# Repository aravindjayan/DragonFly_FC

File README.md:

# DragonFly Flight Controller

DragonFly Flight Controller is an open hardware, low-cost flight controller PCB and experimentation platform for UAV, drone, and embedded systems prototyping. This cost-optimised design uses a two-layer PCB, a budget-conscious bill of materials (BOM), and readily fabricated manufacturing files. Prototype boards were fabricated using the LionCircuits MII service.

The KiCad design targets broad sensor compatibility: it supports most ST LSM6D-series IMUs, while the magnetometer footprint accommodates QMC5883, HMC5883, MMC5983, and IST8310 parts. This makes DragonFly a flexible platform for flight-control experiments, sensor evaluation, and affordable PCB prototyping.

## Repository contents

- `KiCad/Source/` — editable V0.1 board, hierarchical schematic sheets, and project settings.
- `KiCad/Production/` — PCB and project settings for the released `withRibs` manufacturing revision used to generate the production Gerbers.
- `Manufacturing/Gerbers/` — production Gerber layers, drill files, drill maps, and KiCad job file.
- `Photos/` — photo of the assembled PCB.

## Fabrication

Send all files in `Manufacturing/Gerbers/` to your PCB fabricator as one fabrication package. The set includes front and back copper, solder mask, silkscreen, paste, board outline, plated and non-plated drill files, drill maps, and the Gerber job file. Confirm your fabricator accepts these Gerber formats and review the generated previews before ordering.

The released board includes an external rib frame (`withRibs`) for fabrication. Use the matching board in `KiCad/Production/` when reviewing this manufacturing package. `KiCad/Source/` retains the editable source project from the main V0.1 design directory.

## Opening the design

Open `KiCad/Source/dragonfly_v0_1.kicad_pro` in KiCad to work with the source design. Open `KiCad/Production/Dragonfly_v0-1_Ribs.kicad_pcb` to inspect the exact released manufacturing board.

## Revision notes

The production files are from the V0.1 `withRibs` release. The original release notes describe it as adding an external rib frame for improved fabrication. Review electrical design, clearances, and fabrication outputs independently before manufacturing or flight use.

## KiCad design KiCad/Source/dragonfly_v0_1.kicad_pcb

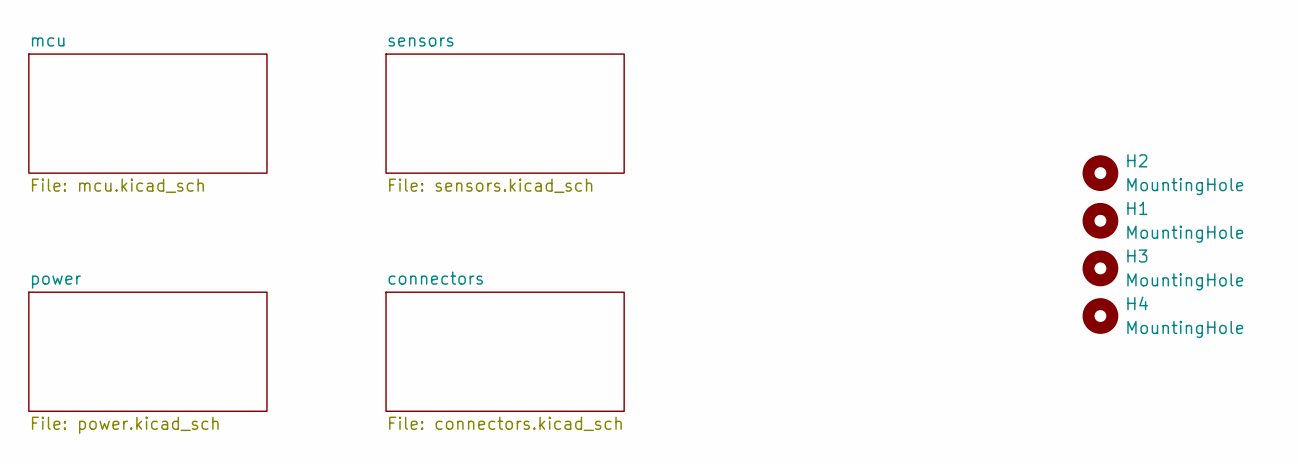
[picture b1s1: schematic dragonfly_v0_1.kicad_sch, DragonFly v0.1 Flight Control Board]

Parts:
H1, H2, H3, H4: MountingHole; MountingHole_2.2mm_M2_ISO14580

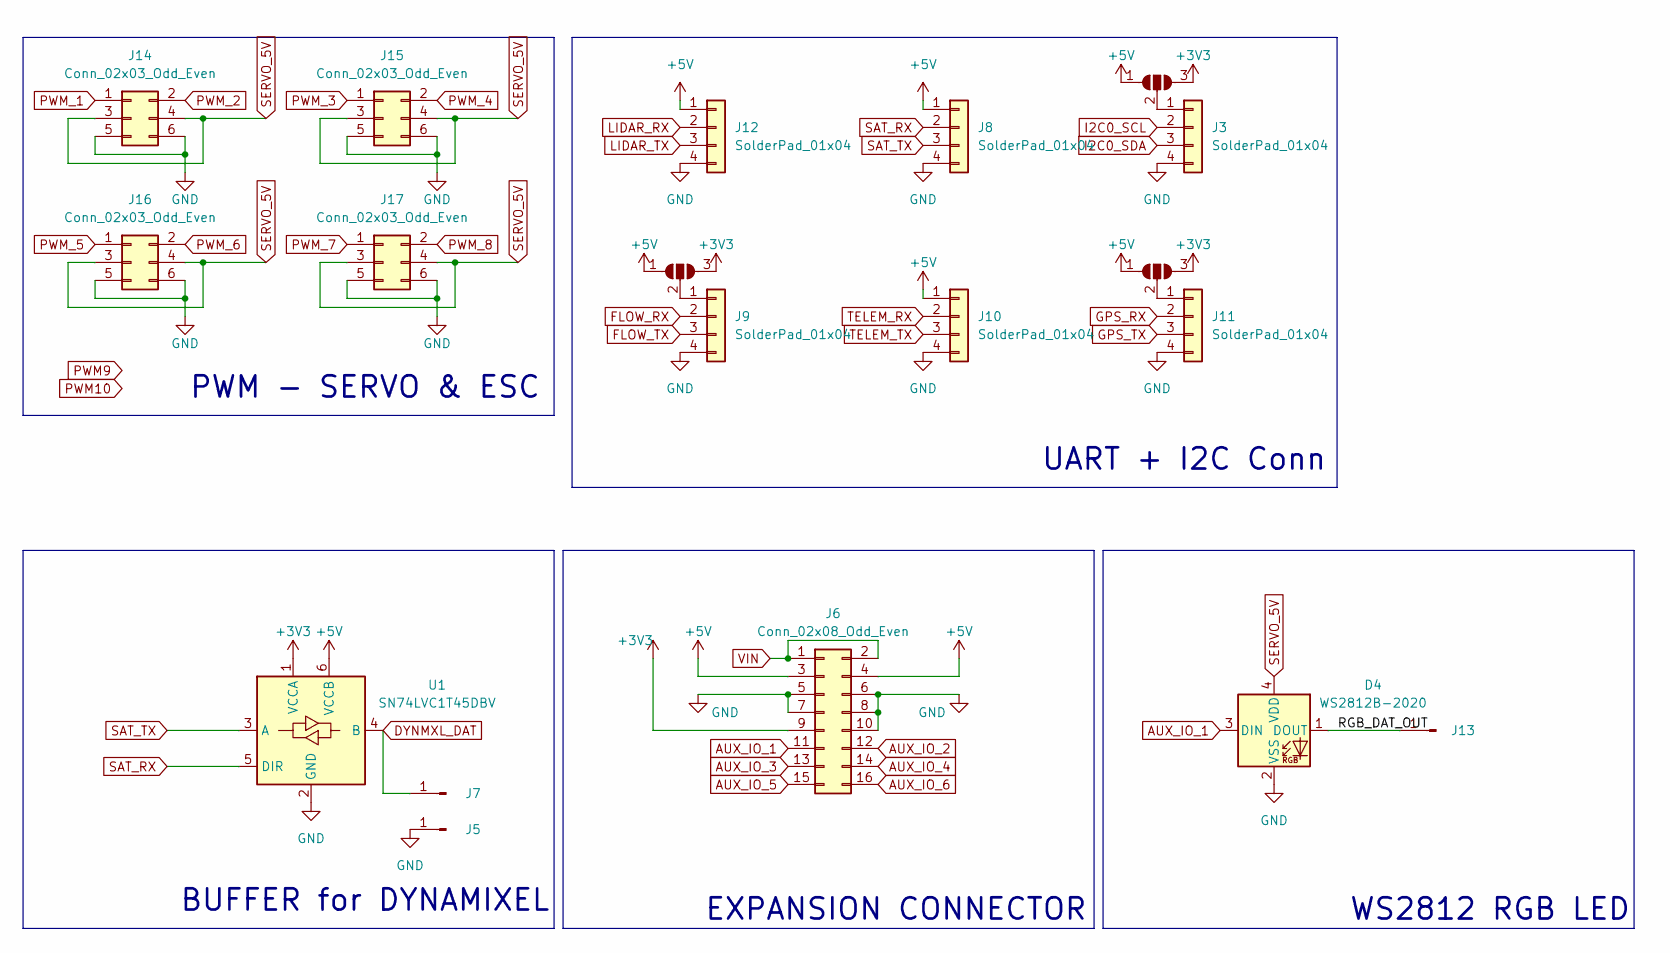
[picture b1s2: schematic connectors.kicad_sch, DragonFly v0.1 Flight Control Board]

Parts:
D4: WS2812B-2020; LED_WS2812B-2020_PLCC4_2.0x2.0mm
J3, J8, J9, J10, J11, J12: SolderPad_01x04; 4pad_doubleSide_rect_1.7x2mm
J5, J7, J13: SolderPad; SolderWirePad_1x01_SMD_1x2mm
J6: Conn_02x08_Odd_Even; PinSocket_2x08_P2.54mm_Vertical
J14, J15, J16, J17: Conn_02x03_Odd_Even; dragonfly_conn_2x3_graphics
JP1, JP2, JP3: SolderJumper_3_Open; SolderJumper-3_P1.3mm_Open_RoundedPad1.0x1.5mm
U1: SN74LVC1T45DBV; SOT-23-6

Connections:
+3V3: J6.9, JP1.3 (B), JP2.3 (B), JP3.3 (B), U1.1 (VCCA); also elsewhere on the board
+5V: J6.3, J6.4, J8.1, J10.1, J12.1, JP1.1 (A), JP2.1 (A), JP3.1 (A), U1.6 (VCCB); also elsewhere on the board
/connectors/RGB_DAT_OUT: D4.1 (DOUT), J13.1
AUX_IO_1: D4.3 (DIN), J6.11; also elsewhere on the board
AUX_IO_2: J6.12; also elsewhere on the board
AUX_IO_3: J6.13; also elsewhere on the board
AUX_IO_4: J6.14; also elsewhere on the board
AUX_IO_5: J6.15; also elsewhere on the board
AUX_IO_6: J6.16; also elsewhere on the board
DYNMXL_DAT: J7.1, U1.4 (B)
FLOW_RX: J9.2; also elsewhere on the board
FLOW_TX: J9.3; also elsewhere on the board
GND: D4.2 (VSS), J3.4, J5.1, J6.5, J6.6, J6.7, J6.8, J6.10, J8.4, J9.4, J10.4, J11.4, J12.4, J14.5, J14.6, J15.5, J15.6, J16.5, J16.6, J17.5, J17.6, U1.2 (GND); also elsewhere on the board
GPS_RX: J11.2; also elsewhere on the board
GPS_TX: J11.3; also elsewhere on the board
I2C0_SCL: J3.2; also elsewhere on the board
I2C0_SDA: J3.3; also elsewhere on the board
LIDAR_RX: J12.2; also elsewhere on the board
LIDAR_TX: J12.3; also elsewhere on the board
unnamed: J3.1, JP1.2 (C)
unnamed: J9.1, JP2.2 (C)
unnamed: J11.1, JP3.2 (C)
PWM_1: J14.1; also elsewhere on the board
PWM_2: J14.2; also elsewhere on the board
PWM_3: J15.1; also elsewhere on the board
PWM_4: J15.2; also elsewhere on the board
PWM_5: J16.1; also elsewhere on the board
PWM_6: J16.2; also elsewhere on the board
PWM_7: J17.1; also elsewhere on the board
PWM_8: J17.2; also elsewhere on the board
SAT_RX: J8.2, U1.5 (DIR); also elsewhere on the board
SAT_TX: J8.3, U1.3 (A); also elsewhere on the board
SERVO_5V: D4.4 (VDD), J14.3, J14.4, J15.3, J15.4, J16.3, J16.4, J17.3, J17.4; also elsewhere on the board
TELEM_RX: J10.2; also elsewhere on the board
TELEM_TX: J10.3; also elsewhere on the board
VIN: J6.1, J6.2; also elsewhere on the board

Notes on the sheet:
UART + I2C Conn
EXPANSION CONNECTOR
PWM - SERVO & ESC
WS2812 RGB LED
BUFFER for DYNAMIXEL

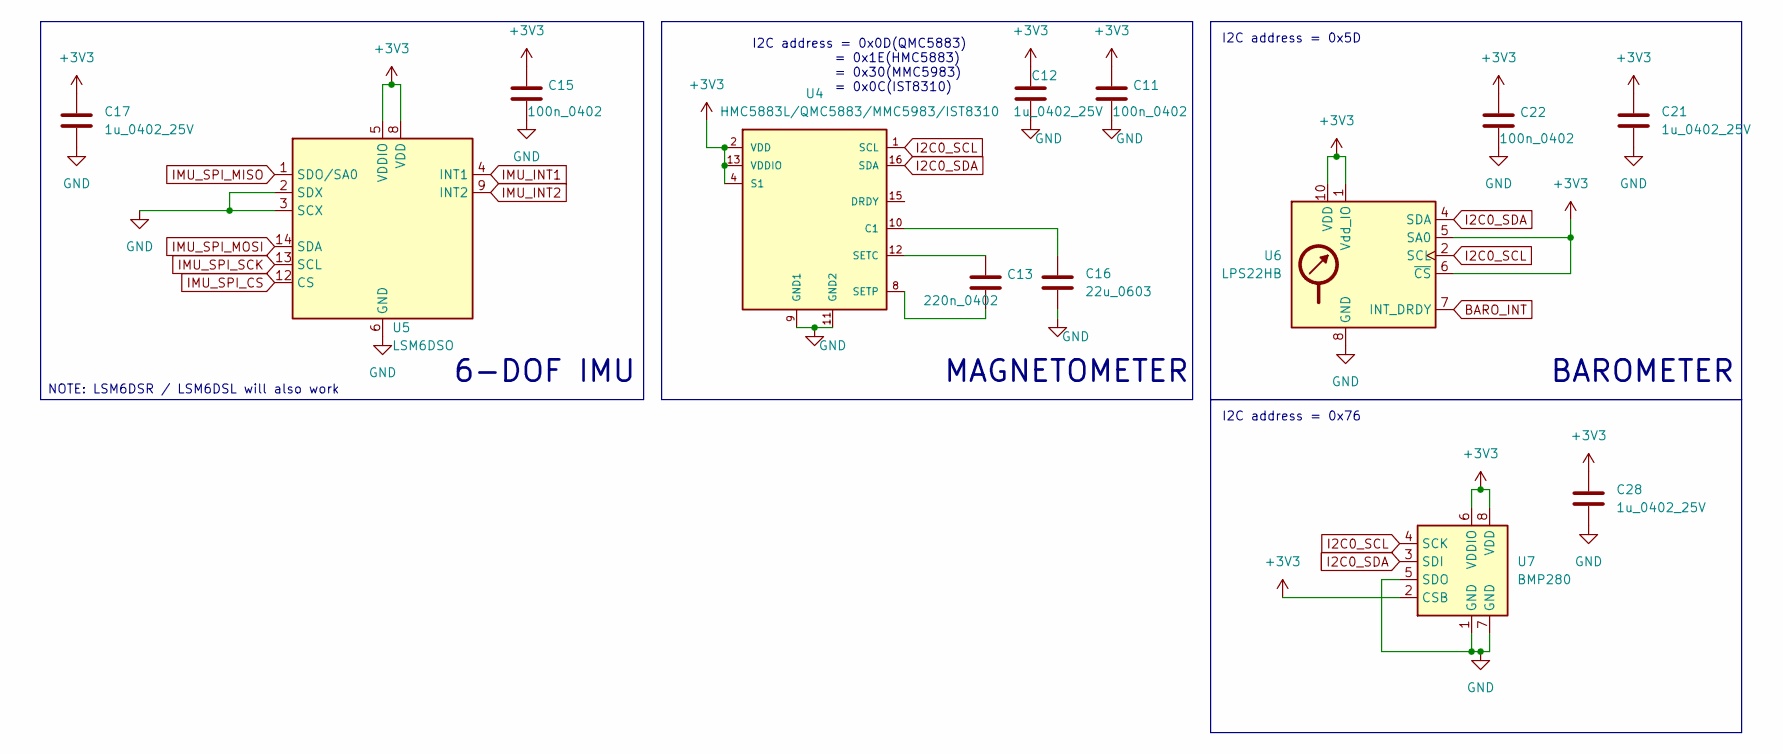
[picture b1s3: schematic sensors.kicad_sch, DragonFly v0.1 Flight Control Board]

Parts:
C11, C15, C22: 100n_0402; C_0402_1005Metric
C12, C17, C21, C28: 1u_0402_25V; C_0402_1005Metric
C13: 220n_0402; C_0402_1005Metric
C16: 22u_0603; C_0603_1608Metric
U4: HMC5883L/QMC5883/MMC5983/IST8310; HMC5883L
U5: LSM6DSO; LGA-14_3x2.5mm_P0.5mm_LayoutBorder3x4y
U6: LPS22HB; LPS22_HLGA10_SNAPEDA
U7: BMP280; BMP280_Bosch_LGA-8_2x2.5mm_P0.65mm_ClockwisePinNumbering

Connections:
+3V3: C11.1, C12.1, C15.1, C17.1, C21.1, C22.1, C28.1, U4.2 (VDD), U4.4 (S1), U4.13 (VDDIO), U5.5 (VDDIO), U5.8 (VDD), U6.1 (Vdd_IO), U6.5 (SA0), U6.6 (~CS), U6.10 (VDD), U7.2 (CSB), U7.6 (VDDIO), U7.8 (VDD); also elsewhere on the board
BARO_INT: U6.7 (INT_DRDY)
GND: C11.2, C12.2, C15.2, C16.2, C17.2, C21.2, C22.2, C28.2, U4.9 (GND1), U4.11 (GND2), U5.2 (SDX), U5.3 (SCX), U5.6 (GND), U5.7 (GND), U6.3 (GND), U6.8 (GND), U6.9 (GND), U7.1 (GND), U7.5 (SDO), U7.7 (GND); also elsewhere on the board
I2C0_SCL: U4.1 (SCL), U6.2 (SCL), U7.4 (SCK); also elsewhere on the board
I2C0_SDA: U4.16 (SDA), U6.4 (SDA), U7.3 (SDI); also elsewhere on the board
IMU_INT1: U5.4 (INT1)
IMU_INT2: U5.9 (INT2)
IMU_SPI_CS: U5.12 (CS); also elsewhere on the board
IMU_SPI_MISO: U5.1 (SDO/SA0); also elsewhere on the board
IMU_SPI_MOSI: U5.14 (SDA); also elsewhere on the board
IMU_SPI_SCK: U5.13 (SCL); also elsewhere on the board
unnamed: C16.1, U4.10 (C1)
unnamed: C13.1, U4.12 (SETC)
unnamed: C13.2, U4.8 (SETP)

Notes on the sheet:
BAROMETER
NOTE: LSM6DSR / LSM6DSL will also work
I2C address = 0x0D(QMC5883) = 0x1E(HMC5883) = 0x30(MMC5983) = 0x0C(IST8310)
I2C address = 0x76
6-DOF IMU
MAGNETOMETER
I2C address = 0x5D

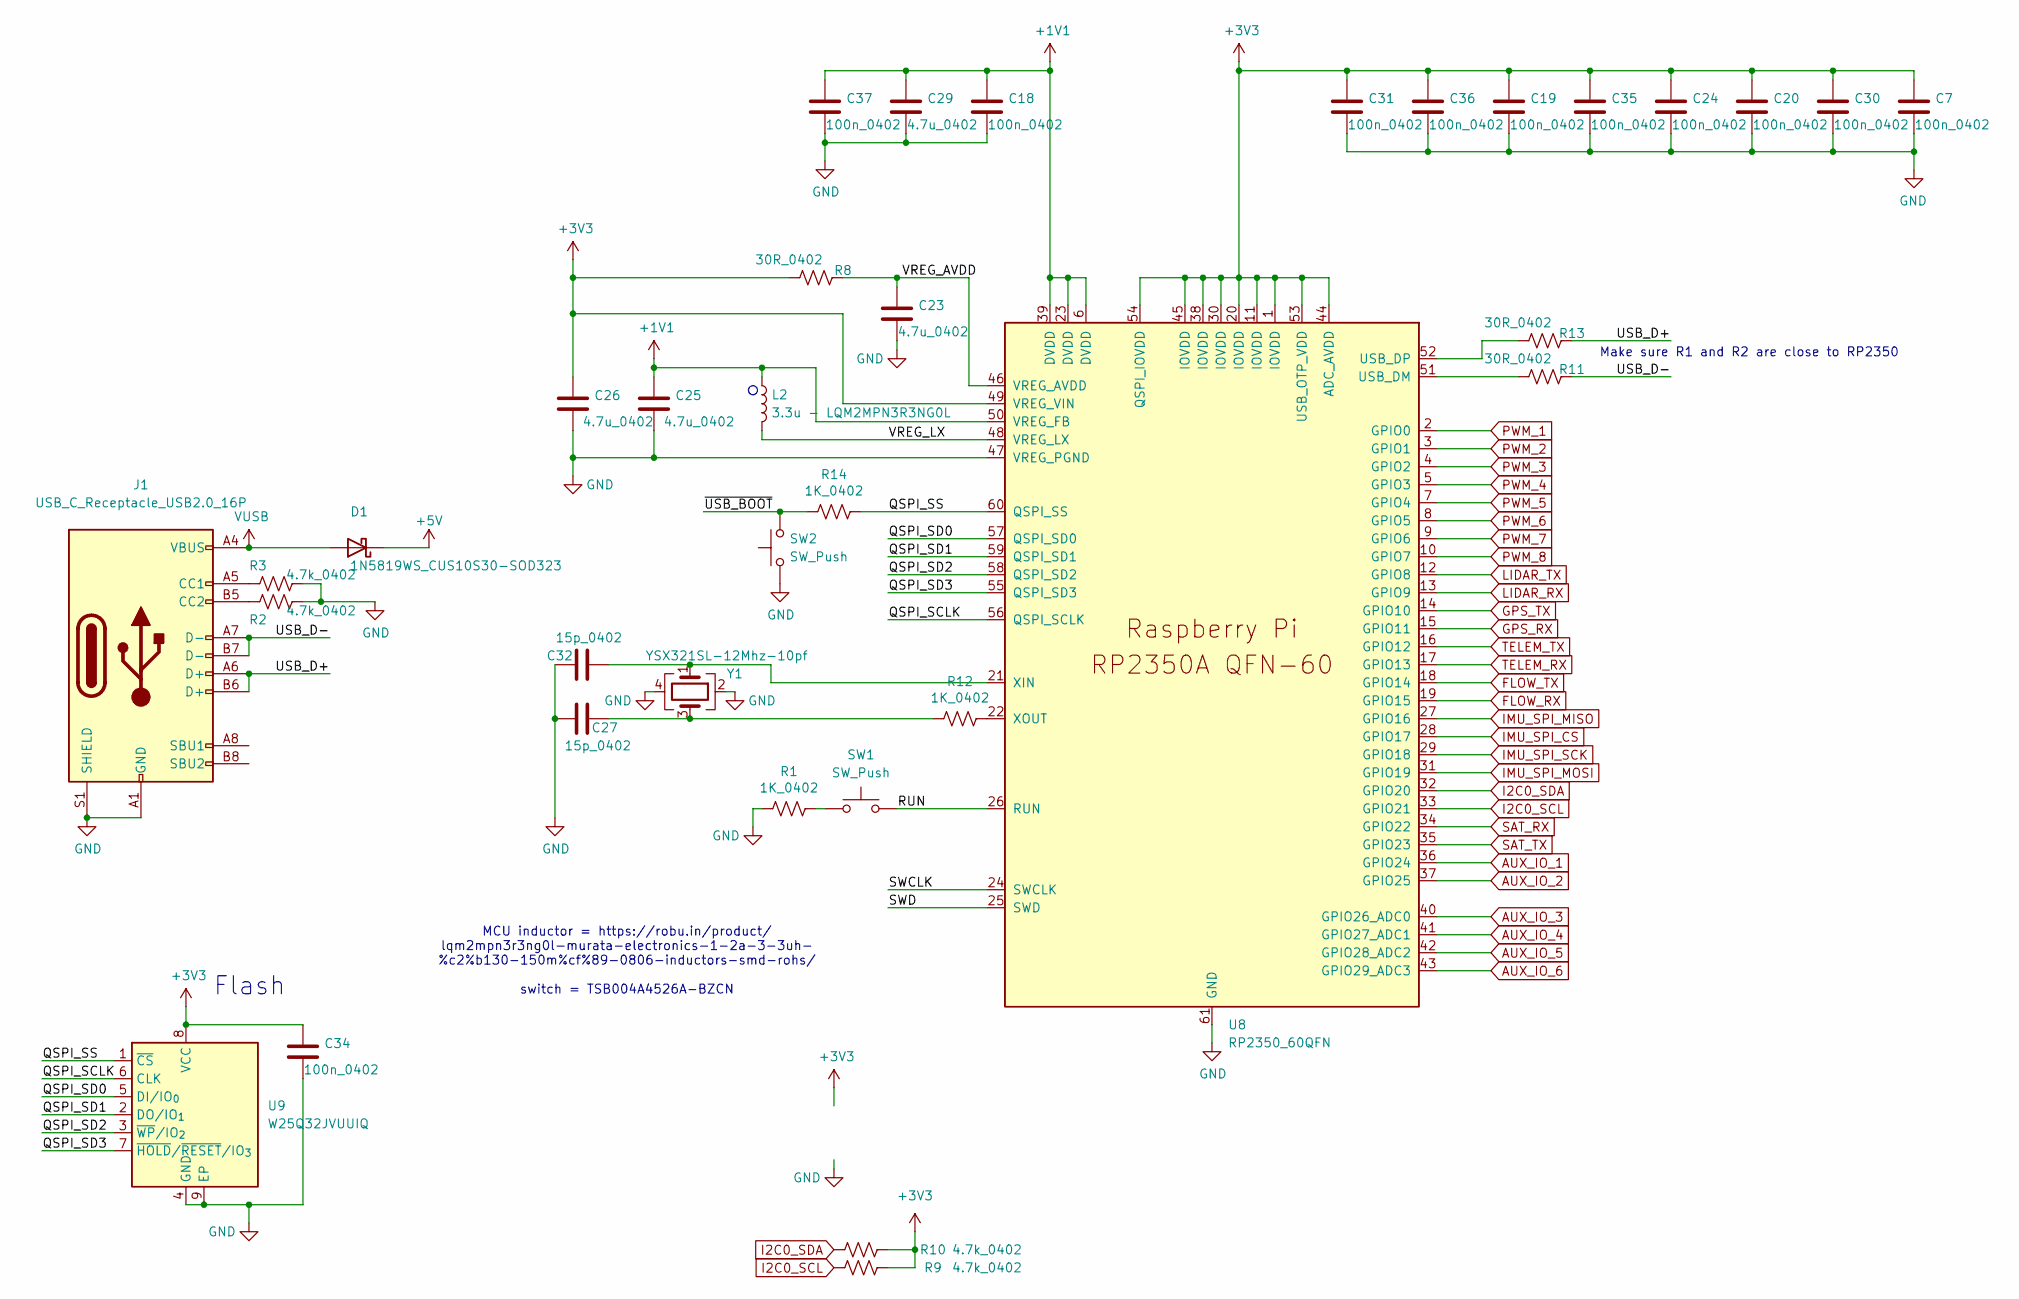
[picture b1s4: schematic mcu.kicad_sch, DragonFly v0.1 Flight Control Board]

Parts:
C7, C18, C19, C20, C24, C30, C31, C34, C35, C36, C37: 100n_0402; C_0402_1005Metric
C23, C29: 4.7u_0402; C_0402_1005Metric
C25, C26: 4.7u_0402; C_0402_SmallPads
C27, C32: 15p_0402; C_0402_1005Metric
D1: 1N5819WS_CUS10S30-SOD323; D_SOD-323
J1: USB_C_Receptacle_USB2.0_16P; USB_C_Receptacle_XKB_U262-16XN-4BVC11
L2: 3.3u - LQM2MPN3R3NG0L; L_Murata_DFE201610P
R1, R12, R14: 1K_0402; R_0402_1005Metric
R2, R3, R9, R10: 4.7k_0402; R_0402_1005Metric
R8, R11, R13: 30R_0402; R_0402_1005Metric
SW1, SW2: SW_Push; rightAngle_Switch_MJTP1117
U8: RP2350_60QFN; QFN-60-1EP_7x7mm_P0.4mm_EP3.4x3.4mm_ThermalVias_RP2350
U9: W25Q32JVUUIQ; Winbond_USON-8-2EP_3x4mm_P0.8mm_EP0.2x0.8mm
Y1: YSX321SL-12Mhz-10pf; Crystal_SMD_3225-4Pin_3.2x2.5mm

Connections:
+1V1: C18.1, C25.1, C29.1, C37.1, L2.1, U8.6 (DVDD), U8.23 (DVDD), U8.39 (DVDD), U8.50 (VREG_FB)
+3V3: C7.1, C19.1, C20.1, C24.1, C26.1, C30.1, C31.1, C34.1, C35.1, C36.1, R8.2, R9.1, R10.1, U8.1 (IOVDD), U8.11 (IOVDD), U8.20 (IOVDD), U8.30 (IOVDD), U8.38 (IOVDD), U8.44 (ADC_AVDD), U8.45 (IOVDD), U8.49 (VREG_VIN), U8.53 (USB_OTP_VDD), U8.54 (QSPI_IOVDD), U9.8 (VCC); also elsewhere on the board
+5V: D1.1 (K); also elsewhere on the board
/mcu/QSPI_SCLK: U8.56 (QSPI_SCLK), U9.6 (CLK)
/mcu/QSPI_SD0: U8.57 (QSPI_SD0), U9.5 (DI/IO_{0})
/mcu/QSPI_SD1: U8.59 (QSPI_SD1), U9.2 (DO/IO_{1})
/mcu/QSPI_SD2: U8.58 (QSPI_SD2), U9.3 (~WP/IO_{2})
/mcu/QSPI_SD3: U8.55 (QSPI_SD3), U9.7 (~HOLD/~RESET/IO_{3})
/mcu/QSPI_SS: R14.1, U8.60 (QSPI_SS), U9.1 (~CS)
/mcu/RUN: SW1.2, U8.26 (RUN)
/mcu/SWCLK: U8.24 (SWCLK)
/mcu/SWD: U8.25 (SWD)
/mcu/USB_D+: J1.A6 (D+), J1.B6 (D+), R13.1
/mcu/USB_D-: J1.A7 (D-), J1.B7 (D-), R11.1
/mcu/VREG_AVDD: C23.1, R8.1, U8.46 (VREG_AVDD)
/mcu/VREG_LX: L2.2, U8.48 (VREG_LX)
/mcu/~USB_BOOT: R14.2, SW2.2
AUX_IO_1: U8.36 (GPIO24); also elsewhere on the board
AUX_IO_2: U8.37 (GPIO25); also elsewhere on the board
AUX_IO_3: U8.40 (GPIO26_ADC0); also elsewhere on the board
AUX_IO_4: U8.41 (GPIO27_ADC1); also elsewhere on the board
AUX_IO_5: U8.42 (GPIO28_ADC2); also elsewhere on the board
AUX_IO_6: U8.43 (GPIO29_ADC3); also elsewhere on the board
FLOW_RX: U8.19 (GPIO15); also elsewhere on the board
FLOW_TX: U8.18 (GPIO14); also elsewhere on the board
GND: C7.2, C18.2, C19.2, C20.2, C23.2, C24.2, C25.2, C26.2, C27.2, C29.2, C30.2, C31.2, C32.2, C34.2, C35.2, C36.2, C37.2, J1.A1 (GND), J1.A12 (GND), J1.B1 (GND), J1.B12 (GND), J1.S1 (SHIELD), R1.2, R2.1, R3.1, SW2.1, U8.47 (VREG_PGND), U8.61 (GND), U9.4 (GND), U9.9 (EP), Y1.2, Y1.4; also elsewhere on the board
GPS_RX: U8.15 (GPIO11); also elsewhere on the board
GPS_TX: U8.14 (GPIO10); also elsewhere on the board
I2C0_SCL: R9.2, U8.33 (GPIO21); also elsewhere on the board
I2C0_SDA: R10.2, U8.32 (GPIO20); also elsewhere on the board
IMU_SPI_CS: U8.28 (GPIO17); also elsewhere on the board
IMU_SPI_MISO: U8.27 (GPIO16); also elsewhere on the board
IMU_SPI_MOSI: U8.31 (GPIO19); also elsewhere on the board
IMU_SPI_SCK: U8.29 (GPIO18); also elsewhere on the board
LIDAR_RX: U8.13 (GPIO9); also elsewhere on the board
LIDAR_TX: U8.12 (GPIO8); also elsewhere on the board
unnamed: C27.1, R12.2, Y1.3
unnamed: J1.A5 (CC1), R3.2
unnamed: J1.B5 (CC2), R2.2
unnamed: R1.1, SW1.1
unnamed: R11.2, U8.51 (USB_DM)
unnamed: R13.2, U8.52 (USB_DP)
unnamed: C32.1, U8.21 (XIN), Y1.1
unnamed: R12.1, U8.22 (XOUT)
PWM_1: U8.2 (GPIO0); also elsewhere on the board
PWM_2: U8.3 (GPIO1); also elsewhere on the board
PWM_3: U8.4 (GPIO2); also elsewhere on the board
PWM_4: U8.5 (GPIO3); also elsewhere on the board
PWM_5: U8.7 (GPIO4); also elsewhere on the board
PWM_6: U8.8 (GPIO5); also elsewhere on the board
PWM_7: U8.9 (GPIO6); also elsewhere on the board
PWM_8: U8.10 (GPIO7); also elsewhere on the board
SAT_RX: U8.34 (GPIO22); also elsewhere on the board
SAT_TX: U8.35 (GPIO23); also elsewhere on the board
TELEM_RX: U8.17 (GPIO13); also elsewhere on the board
TELEM_TX: U8.16 (GPIO12); also elsewhere on the board
VUSB: D1.2 (A), J1.A4 (VBUS), J1.A9 (VBUS), J1.B4 (VBUS), J1.B9 (VBUS)

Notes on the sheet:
Make sure R1 and R2 are close to RP2350
MCU inductor = https://robu.in/product/ lqm2mpn3r3ng0l-murata-electronics-1-2a-3-3uh- %c2%b130-150m%cf%89-0806-inductors-smd-rohs/ switch = TSB004A4526A-BZCN
Flash

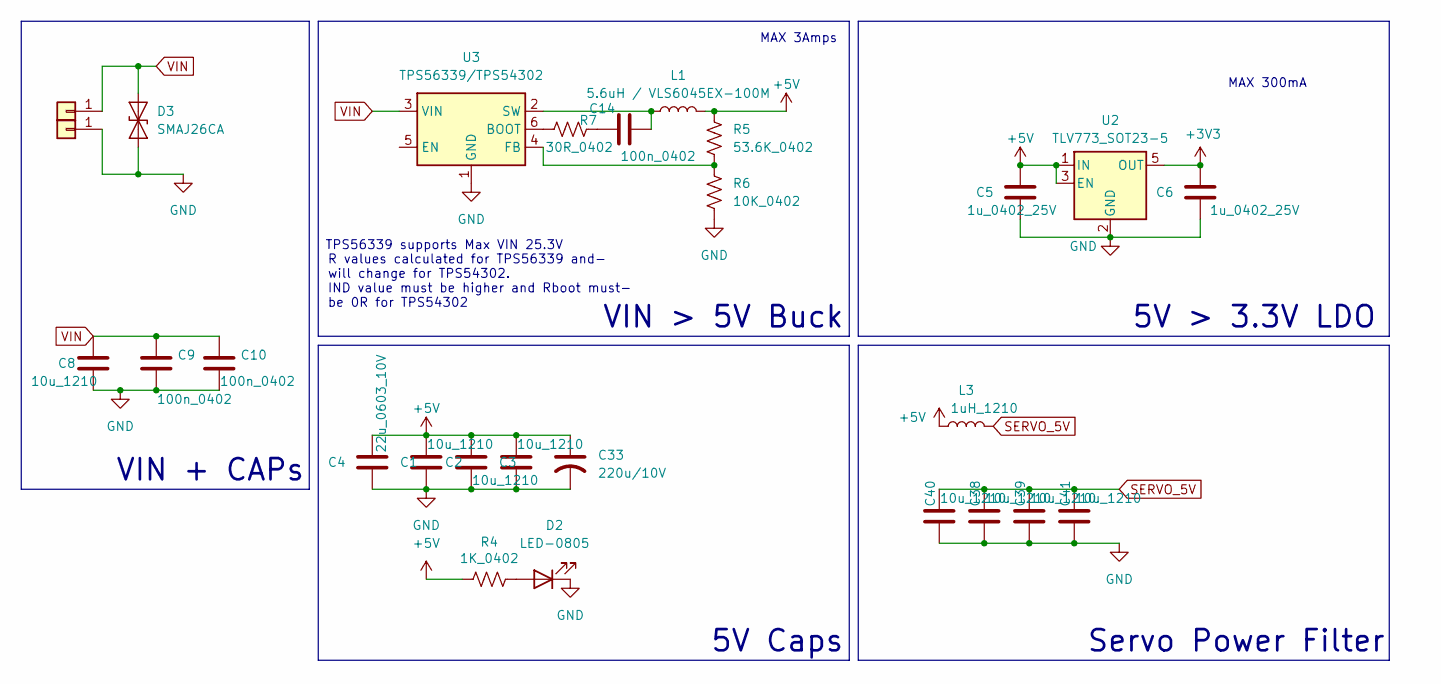
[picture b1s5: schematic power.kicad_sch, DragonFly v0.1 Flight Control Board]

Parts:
C1, C2, C3, C8, C38, C39, C40, C41: 10u_1210; C_1210_3225Metric
C4: 22u_0603_10V; C_0603_1608Metric
C5, C6: 1u_0402_25V; C_0402_1005Metric
C9, C10, C14: 100n_0402; C_0402_1005Metric
C33: 220u/10V; C_Radial_D6.3mm_H5.0mm_P2.50mm
D2: LED-0805; LED_0805_2012Metric
D3: SMAJ26CA; D_SMA
J2, J4: SolderPad; SolderWirePad_1x01_SMD_2x4mm
L1: 5.6uH / VLS6045EX-100M; L_Sunlord_SWPA6045S
L3: 1uH_1210; L_1210_3225Metric_Pad1.42x2.65mm_HandSolder
R4: 1K_0402; R_0402_1005Metric
R5: 53.6K_0402; R_0402_1005Metric
R6: 10K_0402; R_0402_1005Metric
R7: 30R_0402; R_0402_1005Metric
U2: TLV773_SOT23-5; SOT-23-5
U3: TPS56339/TPS54302; SOT-23-6

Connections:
+3V3: C6.2, U2.5 (OUT); also elsewhere on the board
+5V: C1.1, C2.1, C3.1, C4.2, C5.2, C33.1, L1.2, L3.1, R4.2, R5.2, U2.1 (IN), U2.3 (EN); also elsewhere on the board
GND: C1.2, C2.2, C3.2, C4.1, C5.1, C6.1, C8.2, C9.2, C10.2, C33.2, C38.2, C39.2, C40.2, C41.2, D2.1 (K), D3.1 (A1), J2.1, R6.1, U2.2 (GND), U3.1 (GND); also elsewhere on the board
unnamed: C14.1, R7.2
unnamed: D2.2 (A), R4.1
unnamed: R7.1, U3.6 (BOOT)
unnamed: R5.1, R6.2, U3.4 (FB)
unnamed: C14.2, L1.1, U3.2 (SW)
SERVO_5V: C38.1, C39.1, C40.1, C41.1, L3.2; also elsewhere on the board
VIN: C8.1, C9.1, C10.1, D3.2 (A2), J4.1, U3.3 (VIN); also elsewhere on the board

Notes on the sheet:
5V Caps
Servo Power Filter
R values calculated for TPS56339 and- will change for TPS54302. IND value must be higher and Rboot must- be 0R for TPS54302
5V > 3.3V LDO
MAX 3Amps
VIN > 5V Buck
TPS56339 supports Max VIN 25.3V
MAX 300mA
VIN + CAPs

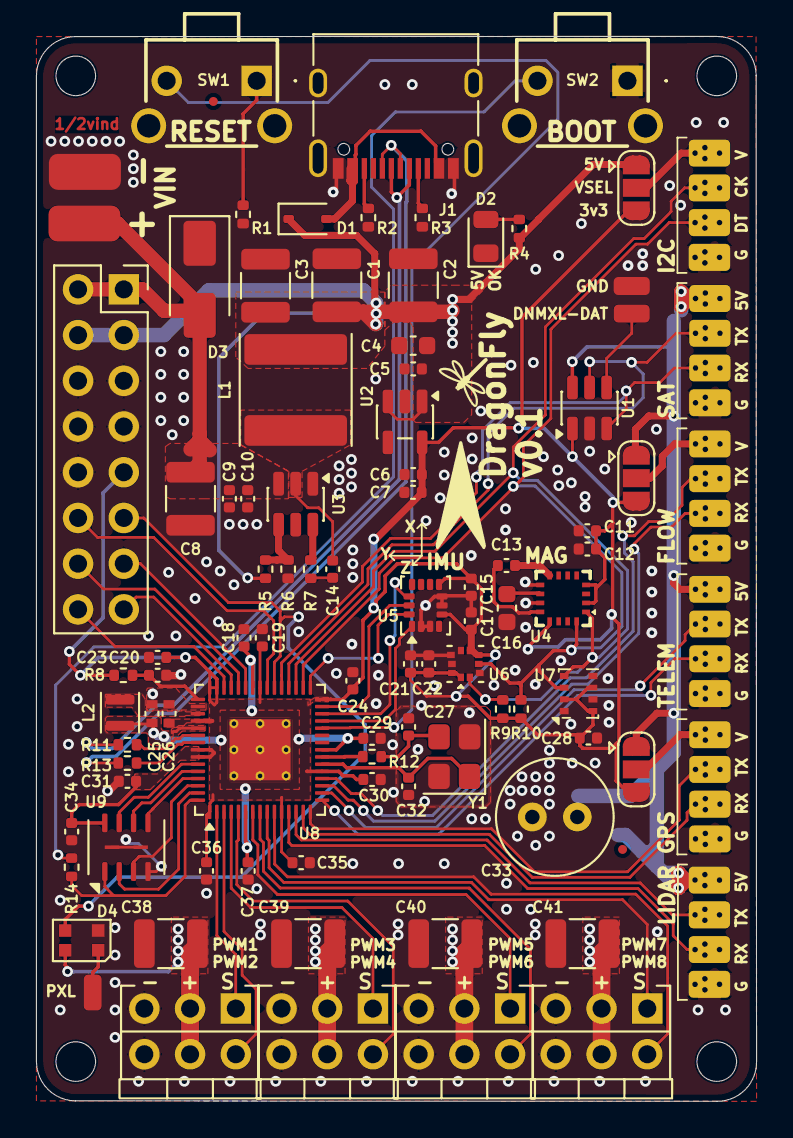
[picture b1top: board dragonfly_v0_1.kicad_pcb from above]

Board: 2 copper layers, 40.0 x 59.2 mm, 98 parts (1 on the bottom side), 70 nets.
